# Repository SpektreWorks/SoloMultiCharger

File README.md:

# SoloMultiCharger
A fully integrated smart circuit to charge up to four Solo Smart Batteries, a Solo hand controller, and two USB devices.

INTRODUCTION

The SpektreWorks Solo Multi-Charger is a multi-battery charging station to be used with the 3DR Solo. It has charging ports for four 3DR Solo Smart Batteries, a Solo hand controller, and two USB devices. SpektreWorks has released all of the design files as open source to the DIY community to build and modify the Multi-Charger. 

The project is made up of a schematic, PCB layout, bill of materials (BOM), and firmware. It is offered as a DIY kit with instructions to make the board, populate it with components, and program the necessary firmware. The schematic and PCB layout are available in Cadsoft Eagle format. The firmware is written in C and compiled with Microchip's XC8 compiler using MPLAB X IDE.

DETAILS

The SpektreWorks Solo Multi-Charger is a single circuit 4-layer PCB that can charge up to four Solo Smart Batteries, the hand controller, and two USB devices. The board requires an external 24VDC power supply capable of at least 5A.

In order to keep the component count and power requirements to a reasonable level, only two batteries charge at a time. Once a battery is done charging, the circuit automatically begins charging the next battery in the queue with no user intervention. The circuit always charges the battery with highest state of charge first. This way, the user only has to wait the shortest possible time to retrieve a fully charged battery.

The Smart Battery and hand controller charge ports are actively current limited. This means that the circuit adjusts the voltage on these ports to not exceed a maximum current value. For the Smart Batteries, the maximum current is 3.3A. The hand controller is 1.5A. These values are adjustable in the firmware, however, it is not recommended to increase those numbers.

The design files in this kit do not include an enclosure of any kind. Users are encouraged to design their own enclosure for the purpose. Keep in mind, however, that this board can generate a lot of heat. Proper heat-sinking and air flow considerations are a very important part of the design.

RELEVANT FILES

PCB/Solo_MultiCharger.sch - Cadsoft Eagle Schematic  
PCB/Solo_MultiCharger.brd - Cadsoft Eagle PCB layout  
PCB/Solo_MultiCharger_BOM.csv - Bill of Materials  
Firmware/Solo_MultiCharger.X/main.c - Source code for charging circuit  
Firmware/Solo_MultiCharger.X/Makefile - Required Makefile for MPLAB  
Firmware/Solo_MultiCharger.X/nbproject - Required directory for MPLAB  
front.jpg - photo of fully assembled front of PCB  
back.jpg - photo of fully assembled back of PCB  

INSTRUCTIONS

**Note: These are extremely abbreviated instructions. We hope that users will suggest what sections need to be elaborated and what sections are fine as they are. As time permits, we will try to expand the instructions until even a relatively inexperienced hobbyist can create their own boards on their own.**

Prerequisites:  
	-Basic familiarity with fabricating PCBs, ordering parts, and soldering  
	-MPLAB X software (free from Microchip) with XC8 compiler (also free)  
	-PICKit3 programming pod  

1. Manufacture the PCB. We did our prototypes at OSHPark.com. We also highly recommend ordering a stencil. This design has a few fine-pitched components that are a little difficult (but not impossible) to solder by hand. Cheap stencils can be ordered from OSHStencils.com.

2. Order the BOM. Every component should be available at digikey.com. If a component is no longer stocked, feel free to contact us and we'll help you find a replacement part.

3. Solder the components to the board.

4. Check the board for shorts. Connect an adjustable current limited power supply and test at 24V. There should only be a few mA of current draw from the supply. If there's more than just a few mA, turn off power and check for solder errors.

5. Check each of the voltages for each switching regulator on the board. For the hand controller and USB outputs, a voltmeter can be applied directly to the charging port pads. The hand controller should show 8.3V and USB should show 5V. The smart battery ports, however, are switched with p-Channel MOSFETs, so they won't always show the required 16.8V. It will be necessary to look at the schematic and probe the capacitors downstream of the inductors of both switching regulators. You should see a steady 16.8V.

5. Open the firmware project in MPLAB X and compile. Confirm there are no compile errors (a couple of “warning (752)” are ok).

6. Connect the board to your computer using a PICKit 3 or equivalent PIC programmer. Program the firmware into the board.

At this point you should be able to connect your 24VDC power supply and start charging batteries, the hand controller, and USB devices. Obviously don't just plug everything in until you've individually tested each port.

Pro Tips:  
	-This board will get hot! Do not place it in an unventilated enclosure. Forced air cooling is always best!  
	-Keep your wires as short as possible. Very long wires can cause large voltage transients when current is suddenly started or stopped.  
	-The four mounting holes are not grounded. If you wish to ground your board to a metal enclosure, you can tap off any solder pad with a negative sign (“-”) next to it.

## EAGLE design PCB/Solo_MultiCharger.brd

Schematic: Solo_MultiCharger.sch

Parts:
C1, C20, C23, C24, C40, C66, C89, C97, C98, C100, C101, C108, C109: 0.1uF; 0805
C2, C5, C7, C18, C25, C26, C28, C39, C41, C46, C48, C50, C52, C67, C70, C72: 1uF 35V; 0805
C3, C4, C21, C22, C42, C43, C45, C68, C69, C81, C82: 10uF 35V 1206; 1206
C6, C27, C44, C47, C51, C71, C102, C103, C104, C105: 0.1uF 35V; 0805
C8, C29, C49, C54, C73: 0.33uF 50V; 0805
C9, C10, C11, C13, C14, C15, C30, C31, C32, C34, C35, C36, C55, C56, C57, C60, C61, C62, C74, C75, C76, C78, C79, C80, C87: 10uF 35V; 0805
C12, C33: 620pF 25V; 0805
C16, C37, C58, C64, C86: 4700pF; 0805
C17, C38: 56pF; 0805
C19, C85, C90, C96, C99: 10uF; 0805
C53, C59, C77: 680pF; 0805
C63: 33pF; 0805
C65, C88: 43pF; 0805
C83, C84, C91, C106: 10uF 16V; 0805
C92, C93, C94, C95, C107, C111: 4.7uF; 0805
C110: UCL1V221MCL6GS; NICHICON_10MM
C112: 1uF; 0805
D1, D4, D8, D12: 1SMB17AT3G; DO-214AA
D2: 1SMA24AT3G; DO-214AC
D3, D5, D6, D7, D13, D14, D16: SBR10E45P5-13; POWERDI-5
D9: 1SMB8.5AT3G; DO-214AA
D10, D11: ESDA8V2-1J; SOD-323
F1: C1F 6; 1206
F2, F3, F4, F5: C1F 4; 1206
F6: C1F 3; 1206
J1: PIC_ICSP_5PIN; SULLINS_XPXC_5PIN
J2: 68021-410HLF; CON_100MIL_2X5
L1, L3: SRR1280-180M; BOURNS_SRR1280
L2: MLZ2012M100WT000; 0805
L4: SRN1060-330M; BOURNS_SRN1060
L5, L6: SRN1060-180M; BOURNS_SRN1060
P1, P2, P3, P4, P5, P6, P7, P8, P9, P10, P11, P12: SOLDER_PAD_(9); SOLDER_PAD_5X8
Q1, Q4, Q6, Q9, Q11, Q14: DMP3017SFG-7; POWERVDFN-8
Q2, Q5, Q8, Q10, Q12, Q15: 2N7002P; SOT-23-3
Q3, Q7, Q13, Q16, Q17: AON6980; DFN5X6B_8L_EP2_ALPHA&OMEGA
R1, R14, R20, R38, R42, R58: 14.7k; 0805
R2, R7, R10, R15, R23, R30, R39, R59, R80: 100k; 0805
R3, R6, R16, R17, R18, R24, R29, R40, R41, R43, R45, R53, R60, R63, R66, R71: 10k; 0805
R4, R26, R44, R61, R79: 10mR; 0805
R5, R21, R46, R47, R62: 2.2; 0805
R8, R27: 2k; 0805
R9, R28, R48, R52, R65: 49.9k 1%; 0805
R11, R32, R56, R69: 10.5k; 0805
R12, R33: 1.82k 1%; 0805
R13, R34: 30; 0805
R19: 100; 0805
R22, R25, R78, R81: 49.9; 0805
R31, R35: 43k; 0805
R36, R54, R74, R76: 15k 1%; 0805
R37, R67, R75, R77: 4.99k 1%; 0805
R49: 3.9k 1%; 0805
R50, R64: 1.62k; 0805
R51: 1.43k; 0805
R55: 7.5k; 0805
R57, R70: 6.81k 1%; 0805
R68: 300; 0805
R72, R73: 10k 1%; 0805
U1, U4, U6, U9, U15: CS30CL; SOT-23-5
U2, U5, U7, U8, U10: MCP19035-AAABE/MF; VFDFN-10_EP
U3: PIC16F1773-I/SS; SSOP-28
U11: MC78M12CDTG; TO-252-3
U12, U13, U16: MCP6L01UT-E/OT; SOT-23-5
U14: MC78M05CDTG; TO-252-3

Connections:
5V: C1.1, C23.1, C40.1, C66.1, C85.1, C89.1, C90.1, C96.1, C97.1, C99.1, C100.1, C108.1, L2.1, R18.2, R68.2, U1.5 (VCC), U4.5 (VCC), U6.5 (VCC), U9.5 (VCC), U12.5 (V+), U13.5 (V+), U14.3 (VOUT), U15.5 (VCC), U16.5 (V+)
5V_USB1: C55.1, C56.1, C57.1, C60.1, C61.1, C62.1, D11.C, J2.9, L5.2, R50.2, R52.2; also elsewhere on the board
5V_USB2: C74.1, C75.1, C76.1, C78.1, C79.1, C80.1, D10.C, J2.10, L6.2, R64.2, R65.2; also elsewhere on the board
!MCLR: C24.1, J1.1 (!MCLR), R18.1, R19.1
+8.3V: D9.C, F6.1, P9.1, R72.2
+16.8(1)V: C2.1, C9.1, C10.1, C11.1, C13.1, C14.1, C15.1, C18.1, C39.1, L1.P$2 (2), Q1.1 (S), Q1.2 (S), Q1.3 (S), Q4.1 (S), Q4.2 (S), Q4.3 (S), Q9.1 (S), Q9.2 (S), Q9.3 (S), R1.2, R8.2, R9.2, R14.2, R38.2; also elsewhere on the board
+16.8(2)V: C25.1, C30.1, C31.1, C32.1, C34.1, C35.1, C36.1, C41.1, C67.1, L3.P$2 (2), Q6.1 (S), Q6.2 (S), Q6.3 (S), Q11.1 (S), Q11.2 (S), Q11.3 (S), Q14.1 (S), Q14.2 (S), Q14.3 (S), R20.2, R27.2, R28.2, R42.2, R58.2; also elsewhere on the board
+24V: C3.1, C4.1, C5.1, C6.1, C21.1, C22.1, C26.1, C27.1, C42.1, C43.1, C45.1, C46.1, C47.1, C50.1, C51.1, C68.1, C69.1, C70.1, C71.1, C81.1, C82.1, F1.2, Q3.2 (D1), Q3.3 (D1), Q3.4 (D1), Q3.EP1@1 (D1), Q3.EP1@2 (D1), Q7.2 (D1), Q7.3 (D1), Q7.4 (D1), Q7.EP1@1 (D1), Q7.EP1@2 (D1), Q13.2 (D1), Q13.3 (D1), Q13.4 (D1), Q13.EP1@1 (D1), Q13.EP1@2 (D1), Q16.2 (D1), Q16.3 (D1), Q16.4 (D1), Q16.EP1@1 (D1), Q16.EP1@2 (D1), Q17.2 (D1), Q17.3 (D1), Q17.4 (D1), Q17.EP1@1 (D1), Q17.EP1@2 (D1), R5.1, R21.1, R46.1, R47.1, R62.1, U11.1 (VIN)
BATT1: D1.C, F2.1, P2.1, R36.2
BATT1_CURR_SENSE: U1.1 (VOUT), U3.13 (RC2/AN14/C[5,6]IN2-/T5CKI/IOCC2)
BATT1_SRC1: Q2.1 (G), R6.2, U3.9 (RA7/CLKIN/OSC1/IOCA7)
BATT1_V_SENSE: C102.1, R36.1, R37.2, U3.23 (RB2/AN8/OPAIN0-/DAC3OUT1/IOCB2)
BATT2: D4.C, F3.1, P6.1, R54.2
BATT2_CURR_SENSE: U3.14 (RC3/AN15/C[5,6]IN2-/T5CKI/IOCC2), U4.1 (VOUT)
BATT2_SRC1: Q5.1 (G), R17.2, U3.10 (RA6/CLKOUT/C6IN1+/OSC2/IOCA6)
BATT2_SRC2: Q8.1 (G), R29.2, U3.12 (RC1/DAC7OUT1/IOCC1)
BATT2_V_SENSE: C103.1, R54.1, R67.2, U3.22 (RB1/AN10/PRG1IN[0,1]/HIB1/C[1-4]IN3-/OP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)
BATT3: D8.C, F4.1, P8.1, R74.2
BATT3_CURR_SENSE: U3.3 (RA1/AN1/PRG1IN0/IOCA1/C[1-4]IN1-), U6.1 (VOUT)
BATT3_SRC1: Q10.1 (G), R41.2, U3.6 (RA4/OPA1IN0+/DAC4OUT1/T0CKI/IOCA4)
BATT3_SRC2: Q12.1 (G), R45.2, U3.5 (RA3/AN3/VREF+/DAC[1-7]REF0+/C1IN1+/IOCA3)
BATT3_V_SENSE: C104.1, R74.1, R75.2, U3.25 (RB4/AN11/C3IN1+/T5G/IOCB4)
BATT4: D12.C, F5.1, P12.1, R76.2
BATT4_CURR_SENSE: U3.2 (RA0/AN0/IOCA0/C[1-6]IN0-), U9.1 (VOUT)
BATT4_SRC2: Q15.1 (G), R63.2, U3.26 (RB5/AN13/DAC[5,7]REF1-/C4IN2-/T1G/IOCB5)
BATT4_V_SENSE: C105.1, R76.1, R77.2, U3.24 (RB3/AN9/C[1-3]IN2-/OPA2IN0+/IOCB3)
CONTROLLER_ADJ_DAC: C109.1, U3.11 (RC0/DAC5OUT1/T1CKI/T3CKI/T3G/IOCC0), U16.1 (IN+)
CONTROLLER_CURR_SENSE: U3.18 (RC7/AN19/OPA3IN0-/IOCC7), U15.1 (VOUT)
CONTROLLER_EN: R71.2, U3.15 (RC4/AN16/C[5,6]IN3-/T8IN/IOCC4), U7.1 (!SHDN)
CONTROLLER_V_SENSE: C44.1, R72.1, R73.2, U3.21 (RB0/AN12/ZCD/HIB0/C2IN1+/IOCB0)
GND: C1.2, C3.2, C4.2, C5.2, C6.2, C7.2, C9.2, C10.2, C11.2, C13.2, C14.2, C15.2, C19.2, C20.2, C21.2, C22.2, C23.2, C24.2, C26.2, C27.2, C28.2, C30.2, C31.2, C32.2, C34.2, C35.2, C36.2, C40.2, C42.2, C43.2, C44.2, C45.2, C46.2, C47.2, C48.2, C50.2, C51.2, C52.2, C55.2, C56.2, C57.2, C60.2, C61.2, C62.2, C66.2, C68.2, C69.2, C70.2, C71.2, C72.2, C74.2, C75.2, C76.2, C78.2, C79.2, C80.2, C81.2, C82.2, C83.2, C84.2, C85.2, C87.2, C89.2, C90.2, C91.2, C92.2, C93.2, C94.2, C95.2, C96.2, C97.2, C98.2, C99.2, C100.2, C101.2, C102.2, C103.2, C104.2, C105.2, C106.2, C107.2, C108.2, C109.2, C110.-, C111.2, C112.2, D1.A, D2.A, D4.A, D8.A, D9.A, D10.A, D11.A, D12.A, J1.3 (GND), J2.1, J2.2, J2.3, J2.4, P1.1, P4.1, P5.1, P7.1, P10.1, P11.1, Q2.2 (S), Q3.5 (S2), Q3.6 (S2), Q3.7 (S2), Q5.2 (S), Q7.5 (S2), Q7.6 (S2), Q7.7 (S2), Q8.2 (S), Q10.2 (S), Q12.2 (S), Q13.5 (S2), Q13.6 (S2), Q13.7 (S2), Q15.2 (S), Q16.5 (S2), Q16.6 (S2), Q16.7 (S2), Q17.5 (S2), Q17.6 (S2), Q17.7 (S2), R2.1, R6.1, R10.1, R13.1, R15.1, R17.1, R29.1, R30.1, R34.1, R37.1, R39.1, R41.1, R45.1, R49.1, R53.1, R57.1, R59.1, R63.1, R66.1, R67.1, R70.1, R71.1, R73.1, R75.1, R77.1, U1.2 (GND), U2.EP (GND), U3.8 (VSS), U3.19 (VSS), U4.2 (GND), U5.EP (GND), U6.2 (GND), U7.EP (GND), U8.EP (GND), U9.2 (GND), U10.EP (GND), U11.4 (GND/ADJ), U12.2 (V-), U13.2 (V-), U14.4 (GND/ADJ), U15.2 (GND), U16.2 (V-)
unnamed: C7.1, R5.2, R7.2, U2.4 (VIN)
unnamed: C111.1, R7.1, U2.1 (!SHDN)
unnamed: C52.1, R46.2, U8.4 (VIN)
unnamed: C92.1, U2.6 (VCC)
unnamed: D5.A@1 (A), D5.A@2 (A), Q6.5 (D), Q6.6 (D), Q6.7 (D), Q6.8 (D), Q6.EP (D), R10.2
unnamed: C8.1, U2.8 (BOOT)
unnamed: C8.2, L1.P$1 (1), Q3.EP2 (S1D2), U2.9 (PHASE)
unnamed: Q3.1 (G1), U2.10 (HDRV)
unnamed: Q3.8 (G2), U2.7 (LDRV)
unnamed: J1.2 (VCC), R68.1
unnamed: R31.2, U12.3 (IN-), U12.4 (OUT)
unnamed: C87.1, U11.3 (VOUT), U14.1 (VIN)
unnamed: C54.1, U8.8 (BOOT)
unnamed: C54.2, L5.1, Q13.EP2 (S1D2), U8.9 (PHASE)
unnamed: Q13.8 (G2), U8.7 (LDRV)
unnamed: Q13.1 (G1), U8.10 (HDRV)
unnamed: C12.2, C17.2, R9.1, R11.1, R12.2, R31.1, U2.2 (FB)
unnamed: R12.1, R13.2
unnamed: C12.1, R8.1
unnamed: C59.2, C65.2, R52.1, R56.1, R57.2, U8.2 (FB)
unnamed: C72.1, R62.2, U10.4 (VIN)
unnamed: C59.1, R50.1
unnamed: C64.1, C65.1, U8.3 (COMP)
unnamed: C64.2, R56.2
unnamed: C48.1, R47.2, U7.4 (VIN)
unnamed: D3.A@1 (A), D3.A@2 (A), Q4.5 (D), Q4.6 (D), Q4.7 (D), Q4.8 (D), Q4.EP (D), R15.2
unnamed: F3.2, R26.1, U4.4 (VM)
unnamed: C73.1, U10.8 (BOOT)
unnamed: J2.8, R78.2
unnamed: C73.2, L6.1, Q16.EP2 (S1D2), U10.9 (PHASE)
unnamed: Q16.8 (G2), U10.7 (LDRV)
unnamed: C49.1, U7.8 (BOOT)
unnamed: C49.2, L4.1, Q17.EP2 (S1D2), U7.9 (PHASE)
unnamed: Q17.8 (G2), U7.7 (LDRV)
unnamed: Q17.1 (G1), U7.10 (HDRV)
unnamed: J2.7, R81.2
unnamed: C53.1, R51.1
unnamed: C58.1, C63.1, U7.3 (COMP)
unnamed: C58.2, R55.2
unnamed: C2.2, Q1.4 (G), R1.1, R3.2
unnamed: Q2.3 (D), R3.1
unnamed: C16.1, C17.1, U2.3 (COMP)
unnamed: C18.2, Q4.4 (G), R14.1, R16.2
unnamed: C16.2, R11.2
unnamed: C28.1, R21.2, R23.2, U5.4 (VIN)
unnamed: C112.1, R23.1, U5.1 (!SHDN)
unnamed: C95.1, U10.6 (VCC)
unnamed: C107.1, U7.6 (VCC)
unnamed: J2.6, R78.1
unnamed: C29.2, L3.P$1 (1), Q7.EP2 (S1D2), U5.9 (PHASE)
unnamed: Q7.8 (G2), U5.7 (LDRV)
unnamed: Q7.1 (G1), U5.10 (HDRV)
unnamed: C33.2, C38.2, R28.1, R32.1, R33.2, R35.1, U5.2 (FB)
unnamed: R33.1, R34.2
unnamed: C33.1, R27.1
unnamed: C37.1, C38.1, U5.3 (COMP)
unnamed: C37.2, R32.2
unnamed: Q16.1 (G1), U10.10 (HDRV)
unnamed: C77.2, C88.2, R65.1, R69.1, R70.2, U10.2 (FB)
unnamed: Q5.3 (D), R16.1
unnamed: C25.2, Q6.4 (G), R20.1, R24.2
unnamed: Q8.3 (D), R24.1
unnamed: C39.2, Q9.4 (G), R38.1, R40.2
unnamed: Q10.3 (D), R40.1
unnamed: C41.2, Q11.4 (G), R42.1, R43.2
unnamed: Q12.3 (D), R43.1
unnamed: C67.2, Q14.4 (G), R58.1, R60.2
unnamed: Q15.3 (D), R60.1
unnamed: C77.1, R64.1
unnamed: C86.1, C88.1, U10.3 (COMP)
unnamed: C86.2, R69.2
unnamed 104: C83.1, C84.1, C91.1, C106.1, D16.A@1 (A), D16.A@2 (A), L4.2, R48.2, R51.2; also elsewhere on the board
unnamed: R22.1, U3.27 (RB6/DAC[5,7]REF1+/C4IN1+/ICSPCLK)
unnamed: C19.1, C20.1, L2.2, U3.20 (VDD)
unnamed: R19.2, U3.1 (RE3/!MCLR)
unnamed: R25.1, U3.28 (RB7/C5IN1+/DAC[1-7]OUT2/T6IN/ICSPDAT)
unnamed: D6.C, R4.2, U1.3 (VP)
unnamed: D7.C, D13.C, R44.2, U6.3 (VP)
unnamed: D3.C, D5.C, R26.2, U4.3 (VP)
unnamed: D14.C, R61.2, U9.3 (VP)
unnamed: D16.C, R79.2, U15.3 (VP)
unnamed: C29.1, U5.8 (BOOT)
unnamed: C93.1, U5.6 (VCC)
unnamed: C94.1, U8.6 (VCC)
unnamed: R35.2, U13.3 (IN-), U13.4 (OUT)
unnamed: F6.2, R79.1, U15.4 (VM)
unnamed: D6.A@1 (A), D6.A@2 (A), Q1.5 (D), Q1.6 (D), Q1.7 (D), Q1.8 (D), Q1.EP (D), R2.2
unnamed: D7.A@1 (A), D7.A@2 (A), Q9.5 (D), Q9.6 (D), Q9.7 (D), Q9.8 (D), Q9.EP (D), R39.2
unnamed: D13.A@1 (A), D13.A@2 (A), Q11.5 (D), Q11.6 (D), Q11.7 (D), Q11.8 (D), Q11.EP (D), R30.2
unnamed: D14.A@1 (A), D14.A@2 (A), Q14.5 (D), Q14.6 (D), Q14.7 (D), Q14.8 (D), Q14.EP (D), R59.2
unnamed: C53.2, C63.2, R48.1, R49.2, R55.1, R80.1, U7.2 (FB)
unnamed: F4.2, R44.1, U6.4 (VM)
unnamed: F5.2, R61.1, U9.4 (VM)
unnamed: F2.2, R4.1, U1.4 (VM)
unnamed: R80.2, U16.3 (IN-), U16.4 (OUT)
unnamed: J2.5, R81.1
PGC: J1.5 (ICSPCLK), R22.2
PGD: J1.4 (ICSPDAT), R25.2
PWR_IN: C110.+, D2.C, F1.1, P3.1
USB1_EN: R53.2, U3.17 (RC6/AN18/PRG3IN0/C[5,6]IN1-/OPA3OUT/IOC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), U8.1 (!SHDN)
USB2_EN: R66.2, U3.16 (RC5/AN17/OPA3IN0+/T4IN/IOCC5), U10.1 (!SHDN)
V1_ADJ_DAC: C98.1, U3.7 (RA5/AN4/OPA1IN0-/DAC2OUT1/IOCA5), U12.1 (IN+)
V2_ADJ_DAC: C101.1, U3.4 (RA2/AN2/VREF-/DAC[1-7]REF0-/DAC1OUT1/IO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), U13.1 (IN+)

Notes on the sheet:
16.8V for Solo Batteries
5V for USB
8.3V for Hand Controller
BATT1
BATT2
BATT3
BATT4
18uH 4.6A 35mOhm
18uH 3.8A 43mOhm
5V for Logic
10uH
CS30 amplifies voltage drop across sense resistor: Vout = Gain * Rsense * Iload Gain = 100 (for CS30CL) Output swing is restricted to 0.1mV to Vcc-1V. Therefore, with VCC=5V and Rsense=10mOhm, CS30 cannot detect true zero current or current above 4A. Iload Vout 5.5A 4V 5.0A 4V 4.0A 4V 3.0A 3V 2.0A 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
6A Fuse Fast Blow
MCU and PWR IN
DAC signal adjusts current flow in resistor divider to adjust output voltage of regulator by small amounts Vout = (Vfb*R1)/R2 + (0.6*R1-Vdac*R1)/R3 + 0.6 R1 -> Top resistor R2 -> Bottom resistor R3 -> Op Amp resistor When Vdac is set to Vfb (0.6V), output of regulator is unaffected by op amp. Raisi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
DAC signal adjusts current flow in resistor divider to adjust output voltage of regulator by small amounts
20V in 5V out
12V
Assuming all devices on board will draw no more than 100mA, the total power wasted in an LDO is (24V-5V)*100mA = 1.9W. Split the heat dissipation between two bodies by using one LDO to drop from 24V to 12V and a second LDO to drop from 12V to 5V.
33uH 2.8A 72mOhm
10V in 5V out
The MCP19035 has an internally timed soft start, but then both 16.8V sources start up at the same time. Put different RCs on the SHDN pin so they start up differently.
CHANGES: 1. 10uF 35V in 0805 and 1206 packages are about the same price. Might as well change all 1206's to 0805's here.
220uF
ICSP Connector

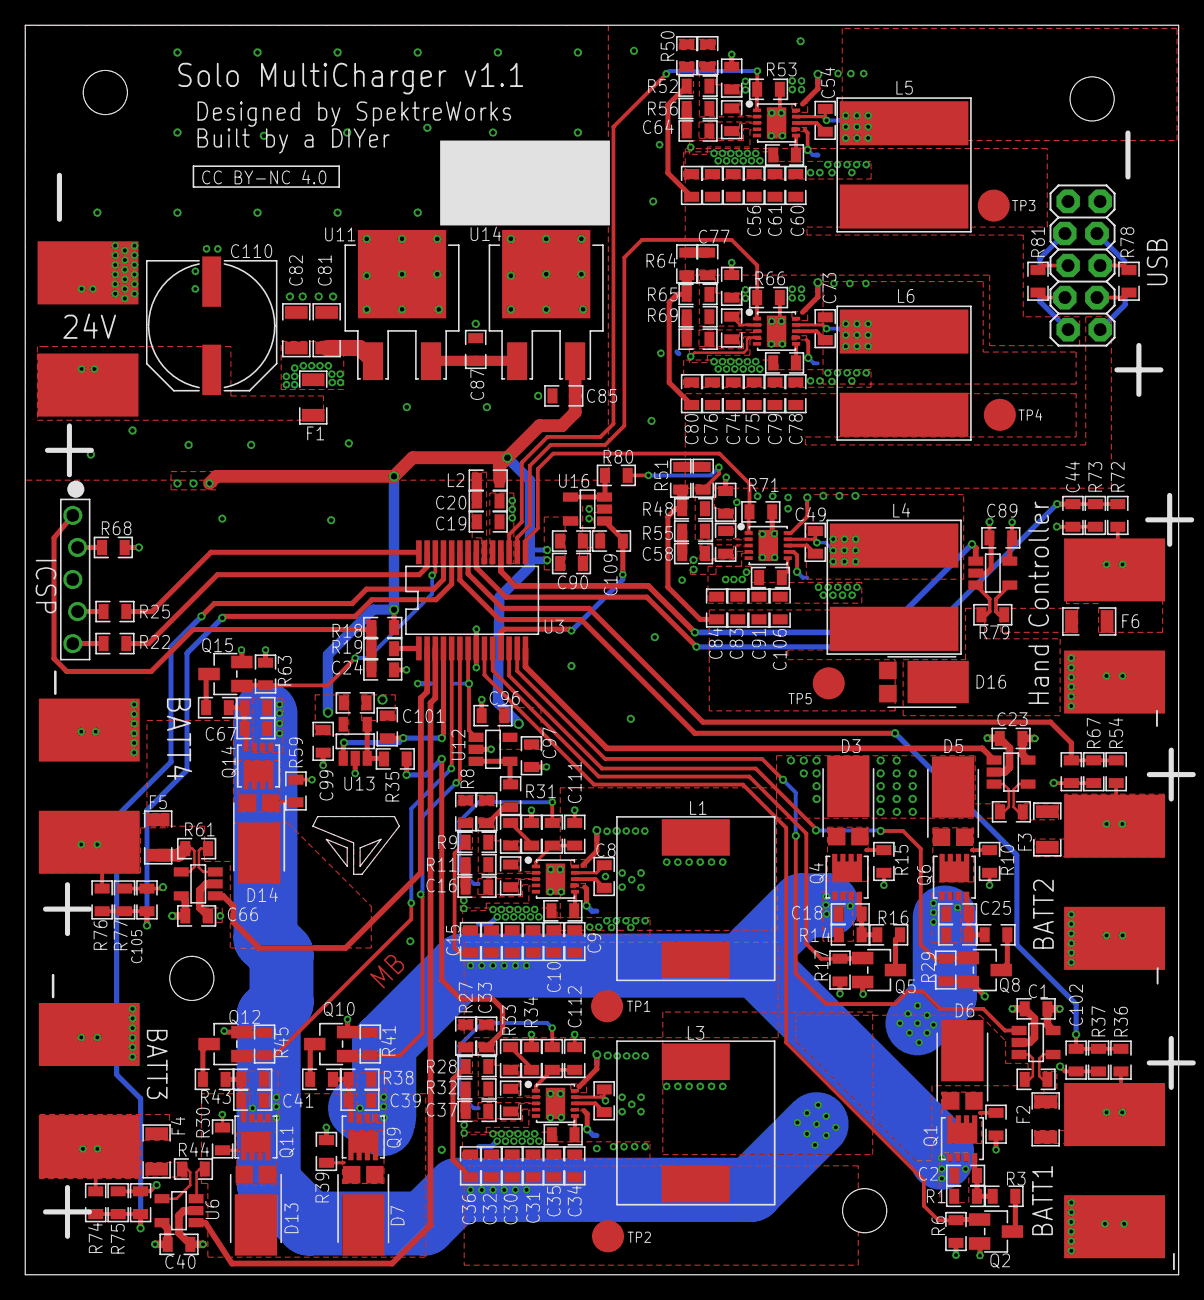
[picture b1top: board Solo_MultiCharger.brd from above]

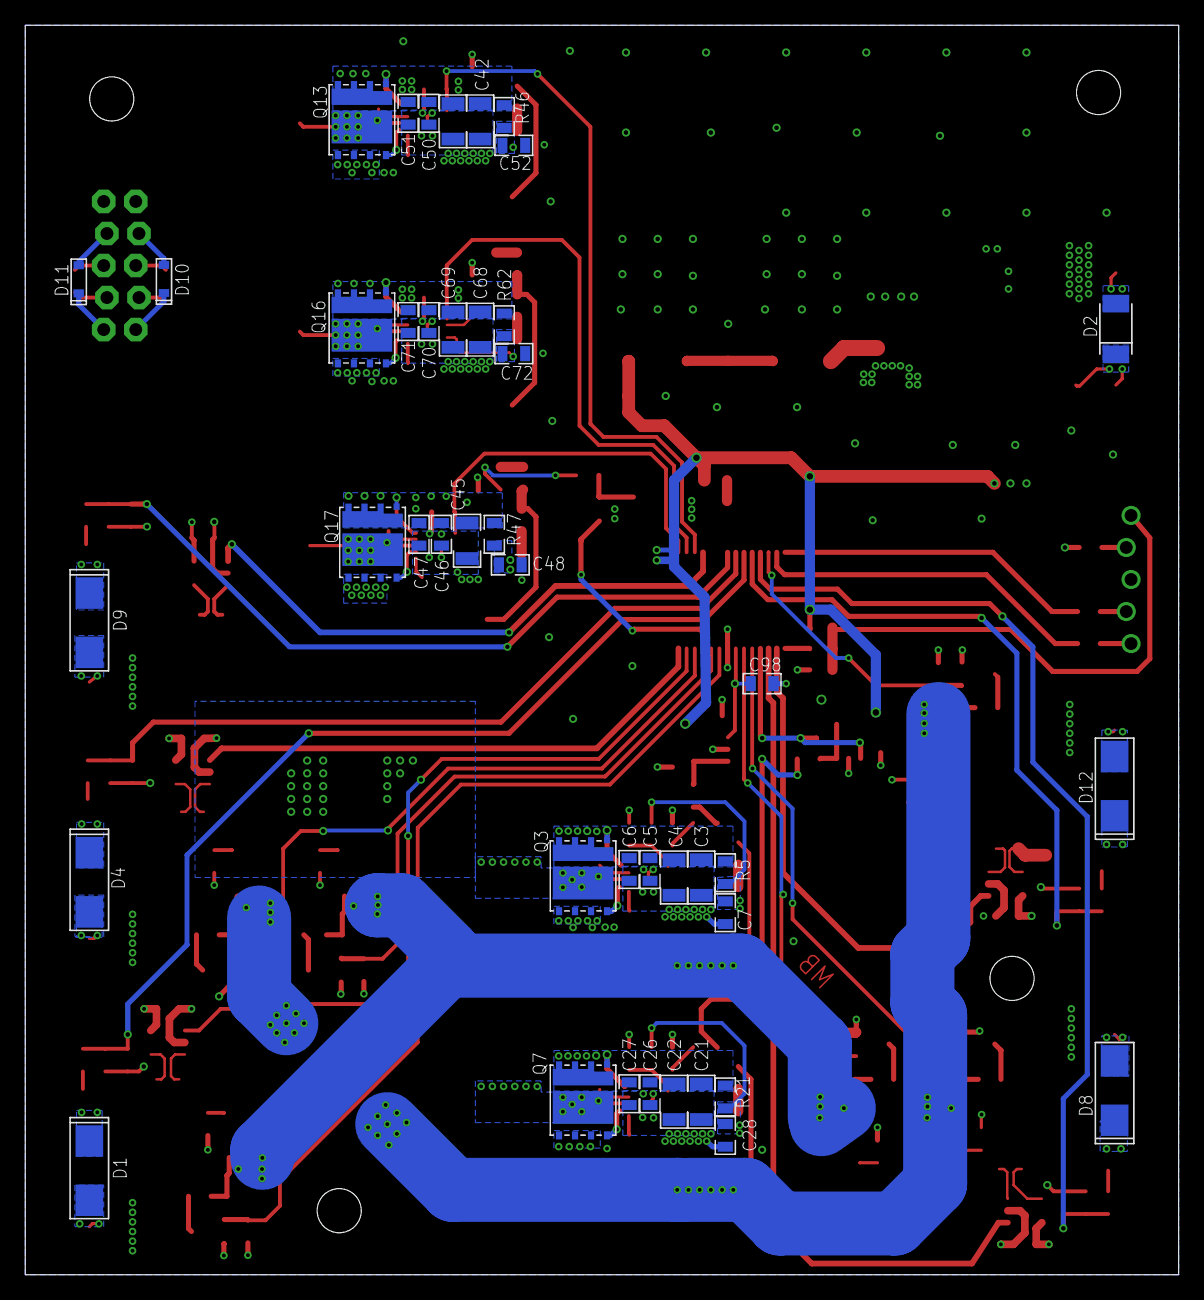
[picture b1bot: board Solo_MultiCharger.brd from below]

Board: 4 copper layers, 91.4 x 99.1 mm, 276 parts (43 on the bottom side), 134 nets.

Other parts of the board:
TP1, TP2, TP3, TP4, TP5: TESTPAD
U$1, U$2, U$3, U$4: MOUNTING_HOLE_M3

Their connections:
5V_USB1: TP3.TP; also elsewhere on the board
5V_USB2: TP4.TP; also elsewhere on the board
+16.8(1)V: TP1.TP; also elsewhere on the board
+16.8(2)V: TP2.TP; also elsewhere on the board
unnamed 104: TP5.TP; also elsewhere on the board

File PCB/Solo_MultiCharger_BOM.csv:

Qty,Value,Package,Parts
13,0.1uF,805,"C1, C20, C23, C24, C40, C66, C89, C97, C98, C100, C101, C108, C109"
10,0.1uF 35V,805,"C6, C27, C44, C47, C51, C71, C102, C103, C104, C105"
5,0.33uF 50V,805,"C8, C29, C49, C54, C73"
5,10uF,805,"C19, C85, C90, C96, C99"
4,10uF 16V,805,"C83, C84, C91, C106"
25,10uF 35V,805,"C9, C10, C11, C13, C14, C15, C30, C31, C32, C34, C35, C36, C55, C56, C57, C60, C61, C62, C74, C75, C76, C78, C79, C80, C87"
11,10uF 35V 1206,1206,"C3, C4, C21, C22, C42, C43, C45, C68, C69, C81, C82"
1,1uF,805,C112
16,1uF 35V,805,"C2, C5, C7, C18, C25, C26, C28, C39, C41, C46, C48, C50, C52, C67, C70, C72"
1,33pF,805,C63
6,4.7uF,805,"C92, C93, C94, C95, C107, C111"
2,43pF,805,"C65, C88"
5,4700pF,805,"C16, C37, C58, C64, C86"
2,56pF,805,"C17, C38"
2,620pF 25V,805,"C12, C33"
3,680pF,805,"C53, C59, C77"
1,UCL1V221MCL6GS,NICHICON_10MM,C110
4,1SMB17AT3G,DO-214AA,"D1, D4, D8, D12"
2,ESDA8V2-1J,SOD-323,"D10, D11"
1,1SMA24AT3G,DO-214AC,D2
7,SBR10E45P5-13,POWERDI-5,"D3, D5, D6, D7, D13, D14, D16"
1,1SMB8.5AT3G,DO-214AA,D9
1,C1F 6,1206,F1
4,C1F 4,1206,"F2, F3, F4, F5"
1,C1F 3,1206,F6
1,68021-410HLF,CON_100MIL_2X5,J2
2,SRR1280-180M,BOURNS_SRR1280,"L1, L3"
1,MLZ2012M100WT000,805,L2
1,SRN1060-330M,BOURNS_SRN1060,L4
2,SRN1060-180M,BOURNS_SRN1060,"L5, L6"
6,DMP3017SFG-7,POWERVDFN-8,"Q1, Q4, Q6, Q9, Q11, Q14"
6,2N7002P,SOT-23-3,"Q2, Q5, Q8, Q10, Q12, Q15"
5,AON6980,DFN5X6B_8L_EP2_ALPHA&OMEGA,"Q3, Q7, Q13, Q16, Q17"
5,2.2,805,"R5, R21, R46, R47, R62"
2,30,805,"R13, R34"
4,49.9,805,"R22, R25, R78, R81"
1,100,805,R19
1,300,805,R68
1,1.43k,805,R51
2,1.62k,805,"R50, R64"
2,1.82k 1%,805,"R12, R33"
4,10.5k,805,"R11, R32, R56, R69"
11,100k,805,"R2, R7, R10, R15, R23, R30, R31, R35, R39, R59, R80"
16,10k,805,"R3, R6, R16, R17, R18, R24, R29, R40, R41, R43, R45, R53, R60, R63, R66, R71"
2,10k 1%,805,"R72, R73"
5,10mR,805,"R4, R26, R44, R61, R79"
6,14.7k,805,"R1, R14, R20, R38, R42, R58"
4,15k 1%,805,"R36, R54, R74, R76"
2,2k,805,"R8, R27"
1,3.9k 1%,805,R49
5,49.9k 1%,805,"R9, R28, R48, R52, R65"
4,4.99k 1%,805,"R37, R67, R75, R77"
2,6.81k 1%,805,"R57, R70"
1,7.5k,805,R55
5,CS30CL,SOT-23-5,"U1, U4, U6, U9, U15"
1,MC78M12CDTG,TO-252-3,U11
3,MCP6L01UT-E/OT,SOT-23-5,"U12, U13, U16"
1,MC78M05CDTG,TO-252-3,U14
5,MCP19035-AAABE/MF,VFDFN-10_EP,"U2, U5, U7, U8, U10"
1,PIC16F1773-I/SS,SSOP-28,U3

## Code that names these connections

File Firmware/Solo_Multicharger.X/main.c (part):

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#pragma config FOSC = INTOSC    // Oscillator Selection Bits (INTOSC oscillator: I/O function on CLKIN pin)
#pragma config WDTE = OFF       // Watchdog Timer Enable (WDT disabled)
#pragma config PWRTE = OFF      // Power-up Timer Enable (PWRT disabled)
#pragma config MCLRE = ON       // MCLR Pin Function Select (MCLR/VPP pin function is MCLR)
#pragma config CP = OFF         // Flash Program Memory Code Protection (Program memory code protection is disabled)
#pragma config BOREN = ON       // Brown-out Reset Enable (Brown-out Reset enabled)
#pragma config CLKOUTEN = OFF   // Clock Out Enable (CLKOUT function is disabled. I/O or oscillator function on the CLKOUT pin)
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#define SRC2_BAY3 LATAbits.LATA3
#define SRC2_BAY4 LATBbits.LATB5

#define CONTROLLER_EN LATCbits.LATC4
#define USB1_EN LATCbits.LATC6
#define USB2_EN LATCbits.LATC5

/* Solo Batteries */
#define DAC_MIN_VOLT 0x3FF
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
#define SRC1 0b00000001
#define SRC2 0b00000010
#define BATT1 0b00000001
#define BATT2 0b00000010
#define BATT3 0b00000100
#define BATT4 0b00001000

/* Globals */

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    LATB = 0;
    LATC = 0;

    TRISAbits.TRISA0 = 1; //BATT4_CURR_SENSE
    TRISAbits.TRISA1 = 1; //BATT3_CURR_SENSE
    TRISAbits.TRISA2 = 0; //V2_ADJ_DAC
    TRISAbits.TRISA3 = 0; //BATT3_SRC2
    TRISAbits.TRISA4 = 0; //BATT3_SRC1
    TRISAbits.TRISA5 = 0; //V1_ADJ_DAC
    TRISAbits.TRISA6 = 0; //BATT2_SRC1
    TRISAbits.TRISA7 = 0; //BATT1_SRC1

    TRISBbits.TRISB0 = 1; //CONTROLLER_V_SENSE
    TRISBbits.TRISB1 = 1; //BATT2_V_SENSE
    TRISBbits.TRISB2 = 1; //BATT1_V_SENSE
    TRISBbits.TRISB3 = 1; //BATT4_V_SENSE
    TRISBbits.TRISB4 = 1; //BATT3_V_SENSE
    TRISBbits.TRISB5 = 0; //BATT4_SRC2
    TRISBbits.TRISB6 = 1; //PGC
    TRISBbits.TRISB7 = 1; //PGD

    TRISCbits.TRISC0 = 0; //CONTROLLER_ADJ_DAC
    TRISCbits.TRISC1 = 0; //BATT2_SRC2
    TRISCbits.TRISC2 = 1; //BATT1_CURR_SENSE
    TRISCbits.TRISC3 = 1; //BATT2_CURR_SENSE
    TRISCbits.TRISC4 = 0; //CONTROLLER_EN
    TRISCbits.TRISC5 = 0; //USB2_EN
    TRISCbits.TRISC6 = 0; //USB1_EN
    TRISCbits.TRISC7 = 1; //CONTROLLER_CURR_SENSE

    ANSELA = 0;
    ANSELAbits.ANSA0 = 1; //BATT4_CURR_SENSE (AN0)
    ANSELAbits.ANSA1 = 1; //BATT3_CURR_SENSE (AN1)

    ANSELB = 0;
    ANSELBbits.ANSB0 = 1; //CONTROLLER_V_SENSE (AN12)
    ANSELBbits.ANSB1 = 1; //BATT2_V_SENSE (AN10)
    ANSELBbits.ANSB2 = 1; //BATT1_V_SENSE (AN8)
    ANSELBbits.ANSB3 = 1; //BATT4_V_SENSE (AN9)
    ANSELBbits.ANSB4 = 1; //BATT3_V_SENSE (AN11)

    ANSELC = 0;
    ANSELCbits.ANSC2 = 1; //BATT1_CURR_SENSE (AN14)
    ANSELCbits.ANSC3 = 1; //BATT2_CURR_SENSE (AN15)
    ANSELCbits.ANSC7 = 1; //CONTROLLER_CURR_SENSE (AN16)
}

void InitTimer1(void)
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
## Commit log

2016-04-21 Increased MAX_AMPS to 3.3A
2016-04-21 Increase min via drill to 12mil
2016-04-21 Added reference to 4-layer board
2016-04-22 A few small layout changes

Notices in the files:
Firmware/Solo_Multicharger.X/main.c:
This program is free software: you can redistribute it and/or modify
it under the terms of the GNU General Public License as published by
the Free Software Foundation, either version 3 of the License, or
(at your option) any later version.
PCB/Solo_MultiCharger.brd:
CC BY-NC 4.0
parts and their libraries:
SparkFun-Aesthetics: Licensing: CC v3.0 Share-Alike You are welcome to use this library for commercial purposes.
